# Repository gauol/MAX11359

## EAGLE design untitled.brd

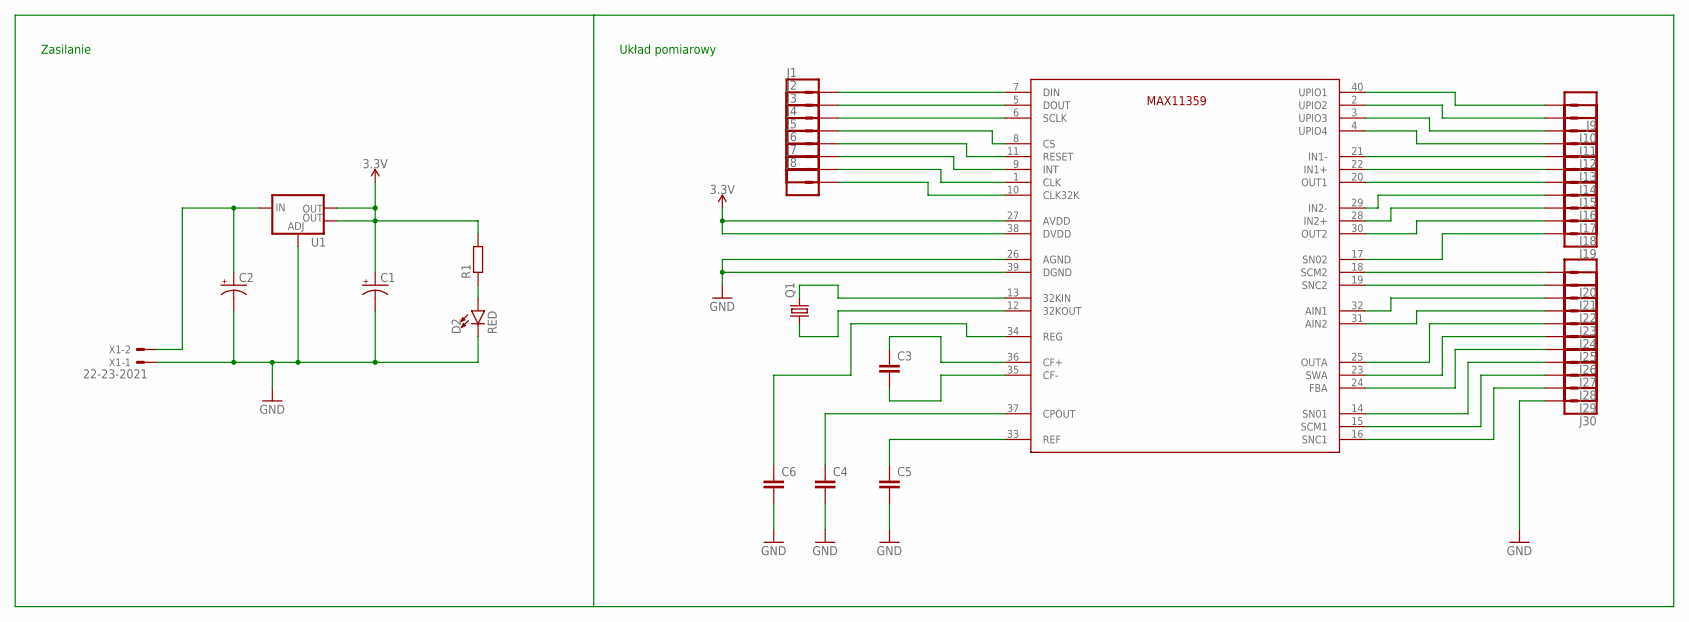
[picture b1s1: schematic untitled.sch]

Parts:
C1, C2: CPOL-US140CLH-1010; 140CLH-1010
C3, C4, C5, C6: C-EUC0805; C0805
D2: RED; LED-1206
J1, J2, J3, J4, J5, J6, J7, J8, J9, J10, J11, J12, J13, J14, J15, J16, J17, J18, J19, J20, J21, J22, J23, J24, J25, J26, J27, J28, J29, J30: CONN_01; 1X01
Q1: CRYSTALHC49UP; HC49UP
R1: R-EU_M0805; M0805
U1: V_REG_LM1117SOT223; SOT223
U$1: MAX11359A; TQFN
X1: 22-23-2021

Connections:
3.3V: C1.+, R1.2, U1.2 (OUT), U1.4 (OUT), U$1.27 (AVDD), U$1.38 (DVDD)
GND: C1.-, C2.-, C4.2, C5.2, C6.2, D2.C, J30.1, U1.1 (ADJ), U$1.26 (AGND), U$1.39 (DGND), X1.1
unnamed: J1.1, U$1.7 (DIN)
unnamed: J2.1, U$1.5 (DOUT)
unnamed: J3.1, U$1.6 (SCLK)
unnamed: J4.1, U$1.8 (CS)
unnamed: J5.1, U$1.11 (RESET)
unnamed: J6.1, U$1.9 (INT)
unnamed: J7.1, U$1.1 (CLK)
unnamed: J8.1, U$1.10 (CLK32K)
unnamed: C3.1, U$1.36 (CF+)
unnamed: C3.2, U$1.35 (CF-)
unnamed: C4.1, U$1.37 (CPOUT)
unnamed: C5.1, U$1.33 (REF)
unnamed: D2.A, R1.1
unnamed: C2.+, U1.3 (IN), X1.2
unnamed: J10.1, U$1.2 (UPIO2)
unnamed: J11.1, U$1.3 (UPIO3)
unnamed: J12.1, U$1.4 (UPIO4)
unnamed: Q1.2, U$1.13 (32KIN)
unnamed: Q1.1, U$1.12 (32KOUT)
unnamed: C6.1, U$1.34 (REG)
unnamed: J9.1, U$1.40 (UPIO1)
unnamed: J13.1, U$1.21 (IN1-)
unnamed: J14.1, U$1.22 (IN1+)
unnamed: J15.1, U$1.20 (OUT1)
unnamed: J16.1, U$1.29 (IN2-)
unnamed: J17.1, U$1.28 (IN2+)
unnamed: J18.1, U$1.30 (OUT2)
unnamed: J19.1, U$1.17 (SN02)
unnamed: J20.1, U$1.18 (SCM2)
unnamed: J21.1, U$1.19 (SNC2)
unnamed: J22.1, U$1.32 (AIN1)
unnamed: J23.1, U$1.31 (AIN2)
unnamed: J24.1, U$1.25 (OUTA)
unnamed: J25.1, U$1.23 (SWA)
unnamed: J26.1, U$1.24 (FBA)
unnamed: J27.1, U$1.14 (SN01)
unnamed: J28.1, U$1.15 (SCM1)
unnamed: J29.1, U$1.16 (SNC1)

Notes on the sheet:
Zasilanie
Układ pomiarowy

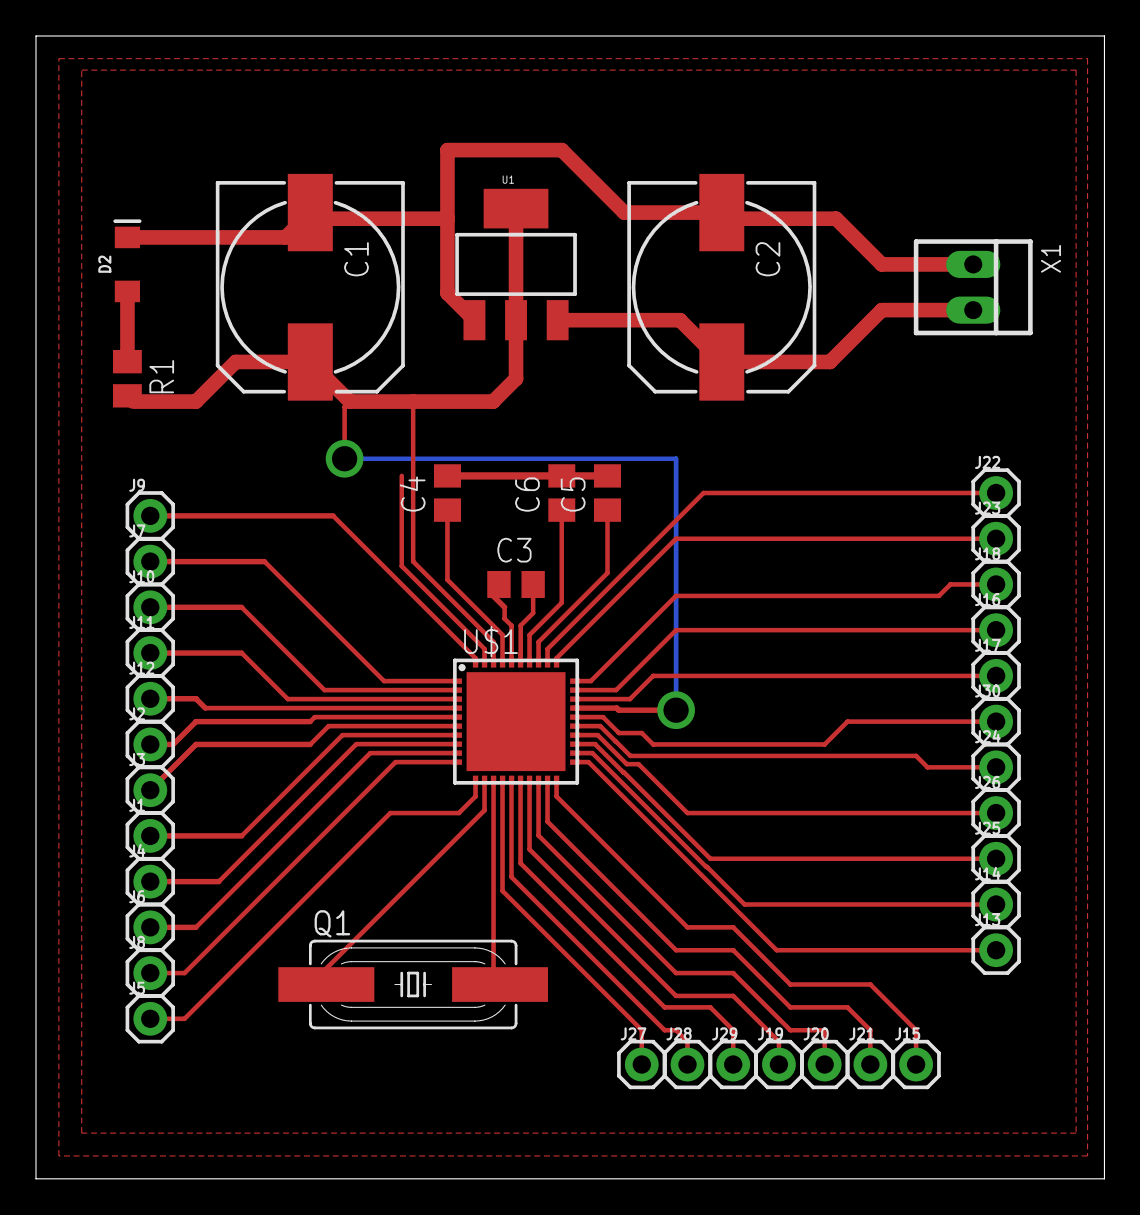
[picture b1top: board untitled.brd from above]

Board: 2 copper layers, 59.4 x 63.5 mm, 42 parts (0 on the bottom side), 40 nets.

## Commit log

2017-04-11 Pierwsza wersja płytki

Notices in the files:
parts and their libraries:
SparkFun-IC-Power: Licensing: Creative Commons ShareAlike 4.0 International - https://creativecommons.org/licenses/by-sa/4.0
